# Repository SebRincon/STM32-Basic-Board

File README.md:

### STM32-Basic-Board

Basic STM32 Board with some basic interface and programmed in C.

PCB Layout                 |        Schematic
:-------------------------:|:-------------------------:
  |  

## Missing Assets Locations
[USB Micro](https://www.we-online.com/catalog/en/COM_MICRO_SMT_TYPE_B_HORIZONTAL_HIGH_CURRENT?sq=629105150521&sp=https%3A%2F%2Fwww.we-online.com%2Fweb%2Fen%2Fwuerth_elektronik%2Fsearchpage.php%3Fsearch%3D629105150521#629105150521)

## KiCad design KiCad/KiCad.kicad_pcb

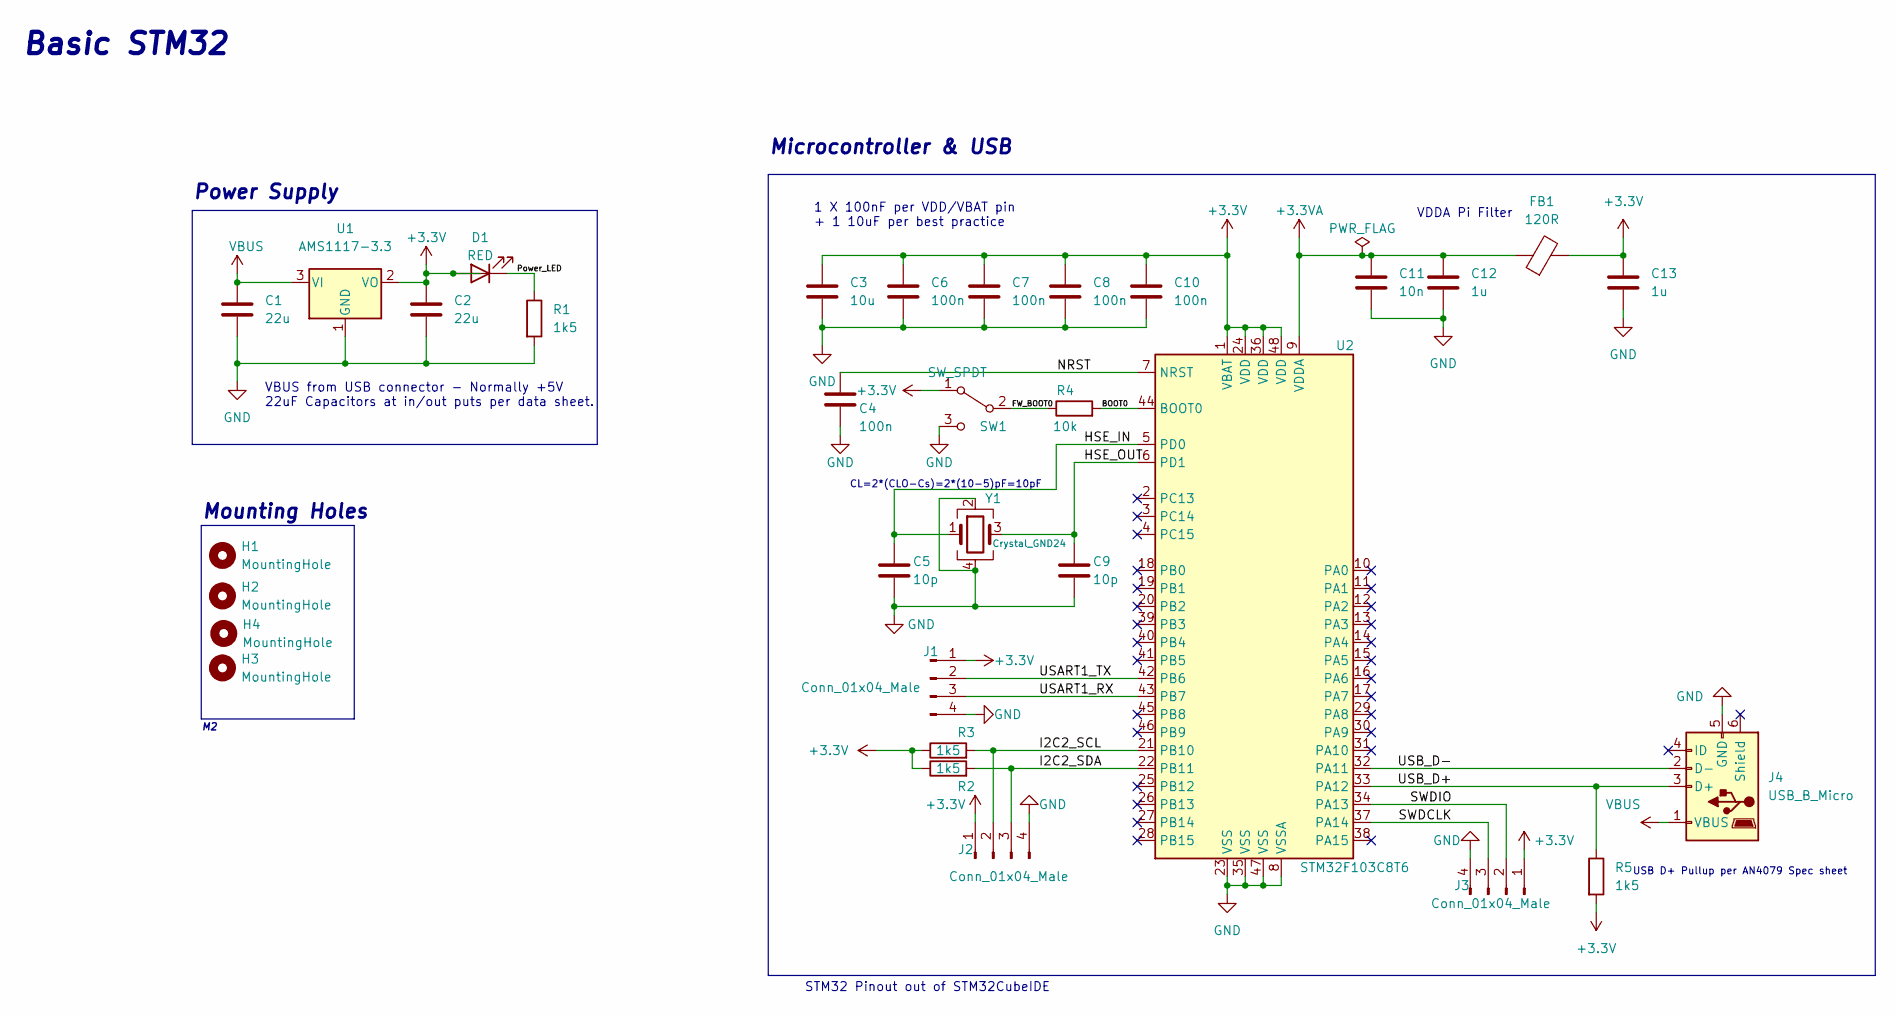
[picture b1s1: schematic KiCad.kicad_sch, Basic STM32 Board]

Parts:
C1, C2: 22u; C_0805_2012Metric
C3: 10u; C_0603_1608Metric
C4, C6, C7, C8, C10: 100n; C_0402_1005Metric
C5, C9: 10p; C_0402_1005Metric
C11: 10n; C_0402_1005Metric
C12, C13: 1u; C_0402_1005Metric
D1: RED; LED_0603_1608Metric
FB1: 120R; L_0603_1608Metric
H1, H2, H3, H4: MountingHole; MountingHole_2.2mm_M2
J1, J2, J3: Conn_01x04_Male; PinHeader_1x04_P2.00mm_Vertical
J4: USB_B_Micro; USB_Micro-B_Molex_47346-0001
R1, R2, R3, R5: 1k5; R_0402_1005Metric
R4: 10k; R_0402_1005Metric
SW1: SW_SPDT; SW_SPDT_PCM12
U1: AMS1117-3.3; SOT-223-3_TabPin2
U2: STM32F103C8T6; LQFP-48_7x7mm_P0.5mm
Y1: Crystal_GND24; Crystal_SMD_3225-4Pin_3.2x2.5mm

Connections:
+3.3V: C2.1, C3.1, C6.1, C7.1, C8.1, C10.1, C13.1, D1.2 (A), FB1.2, J1.1, J2.1, J3.1, R2.1, R3.1, R5.2, SW1.1 (A), U1.2 (VO), U2.1 (VBAT), U2.24 (VDD), U2.36 (VDD), U2.48 (VDD)
+3.3VA: C11.1, C12.1, FB1.1, U2.9 (VDDA)
/BOOT0: R4.2, U2.44 (BOOT0)
/FW_BOOT0: R4.1, SW1.2 (B)
/HSE_IN: C5.1, U2.5 (PD0), Y1.1
/HSE_OUT: C9.1, U2.6 (PD1), Y1.3
/I2C2_SCL: J2.2, R2.2, U2.21 (PB10)
/I2C2_SDA: J2.3, R3.2, U2.22 (PB11)
/NRST: C4.1, U2.7 (NRST)
/Power_LED: D1.1 (K), R1.1
/SWDCLK: J3.3, U2.37 (PA14)
/SWDIO: J3.2, U2.34 (PA13)
/USART1_RX: J1.3, U2.43 (PB7)
/USART1_TX: J1.2, U2.42 (PB6)
/USB_D+: J4.3 (D+), R5.1, U2.33 (PA12)
/USB_D-: J4.2 (D-), U2.32 (PA11)
GND: C1.2, C2.2, C3.2, C4.2, C5.2, C6.2, C7.2, C8.2, C9.2, C10.2, C11.2, C12.2, C13.2, J1.4, J2.4, J3.4, J4.5 (GND), R1.2, SW1.3 (C), U1.1 (GND), U2.8 (VSSA), U2.23 (VSS), U2.35 (VSS), U2.47 (VSS), Y1.2, Y1.4
VBUS: C1.1, J4.1 (VBUS), U1.3 (VI)

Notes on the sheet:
Microcontroller & USB
VDDA Pi Filter
Mounting Holes
VBUS from USB connector - Normally +5V 22uF Capacitors at in/out puts per data sheet.
STM32 Pinout out of STM32CubeIDE
Basic STM32
1 X 100nF per VDD/VBAT pin + 1 10uF per best practice
CL=2*(CLO-Cs)=2*(10-5)pF=10pF
Power Supply
USB D+ Pullup per AN4079 Spec sheet

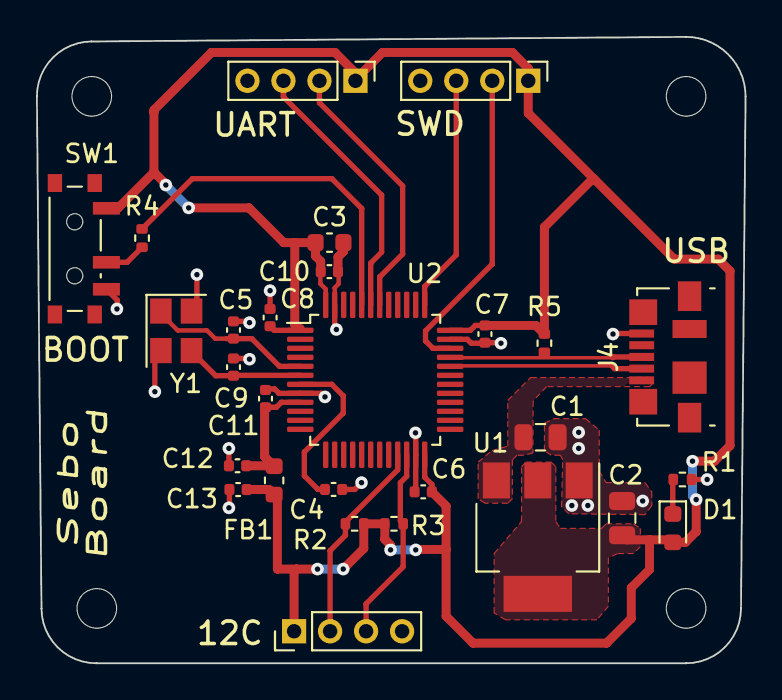
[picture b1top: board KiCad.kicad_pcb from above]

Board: 2 copper layers, 39.4 x 34.8 mm, 32 parts (0 on the bottom side), 18 nets.

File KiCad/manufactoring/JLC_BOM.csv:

Designator,Comment,Footprint,JLCPCB Part #
"C1, C2, ",22u,Capacitor_SMD:C_0805_2012Metric,C140362
"C3, ",10u,Capacitor_SMD:C_0603_1608Metric,C19702
"C4, C6, C7, C8, C10, ",100n,Capacitor_SMD:C_0402_1005Metric,C131394
"C5, C9, ",10p,Capacitor_SMD:C_0402_1005Metric,C469620
"C11, ",10n,Capacitor_SMD:C_0402_1005Metric, C525224
"C12, C13, ",1u,Capacitor_SMD:C_0402_1005Metric,C29266
"D1, ",RED,LED_SMD:LED_0603_1608Metric,C389517
"FB1, ",120R,Inductor_SMD:L_0603_1608Metric,C42102
"J1, J2, J3, ",Conn_01x04_Male,Connector_PinHeader_2.00mm:PinHeader_1x04_P2.00mm_Vertical,C541858
"J4, ",USB_B_Micro,Connector_USB:USB_Micro-B_Wuerth_629105150521,C132560
"R1, R2, R3, R5, ",1k5,Resistor_SMD:R_0402_1005Metric,C25867
"R4, ",10k,Resistor_SMD:R_0402_1005Metric,C269674
"SW1, ",SW_SPDT,Button_Switch_SMD:SW_SPDT_PCM12,C431541
"U1, ",AMS1117-3.3,Package_TO_SOT_SMD:SOT-223-3_TabPin2,C6186
"U2, ",STM32F103C8T6,Package_QFP:LQFP-48_7x7mm_P0.5mm,C8734
"Y1, ",Crystal_GND24,Crystal:Crystal_SMD_3225-4Pin_3.2x2.5mm_HandSoldering,C518160

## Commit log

2022-10-03 Inital Commit
2022-10-03 Added UART & SPI Support pinout
2022-10-03 Added annotation to schematic
2022-10-03 Added Footprints
2022-10-05 Setup the basics for a common PCB
2022-10-05 Routed STM32 & Various Important components
    Routed the Crystal as well as the Capacitors
2022-10-05 Swapped switch footprint
2022-10-05 Fixed route line bugs & routed pheriphials
2022-10-05 Routed power supply components
2022-10-05 Added Mounting holes and arranged board outline
2022-10-06 Routed the sensitive components
2022-10-06 Routed Pinout Connectors & other signal pins
2022-10-06 Finished Power Routing
2022-10-06 Fixed some design bugs and added board title
2022-10-06 Generated BOM Files
2022-10-06 Generated Gerbers
2022-10-06 Included completed 3D View of board
2022-10-06 Updated readme with images
2022-10-08 Sourced parts & Changed some components
2022-10-08 Recreated the gerbers
2022-10-08 Remade the BOM & CPL for JLCPCB
